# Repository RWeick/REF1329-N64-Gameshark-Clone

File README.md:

# REF1329-N64-Gameshark-Pro-Clone
This is a fully functional Nintendo 64 GameShark clone. It implements the original LZ9FC17 GAL on an Altera EPM240, and fully supports all functionality to include: parallel port, 7 segment display, and the GS button.

The LZ9FC17 GAL is the same for both the N64 Gameshark and the N64 Gameshark Pro. All N64 Gameshark and Action Replay firmwares work with this clone.

This is compatible with the Sanni Cartridge Reader's N64 Gameshark programming function as well as the EMS hacked firmware that was released for the first ever Gameshark / Action Replay clone.

The upper EEPROM contains the high bytes of the BIN, and the lower EEPROM contains the low bytes of the BIN. The 2x5 10 pin connector is mapped to the standard Altera USB Blaster pinout for programming. Happy making.

Huge shoutout to @Parasyte for his ceaseless guidance, mentorship, and encouragement, as well as for originally documenting the hardware registers of the N64 Gameshark. This would not exist without him.

Huge shoutout to the [N64Brew](https://n64brew.dev/wiki/Main_Page) community, who have provided countless resources and documentation that enabled me to complete this project.

Huge shoutout to @Jhynjhiruu for determining that my original reconstruction wasn't perfectly faithful to the original chip. With his discoveries, the logic here is now complete.

The Various Gameshark Firmwares directory contains every known firmware in existence. All US firmwares have been collected and preserved there as well as all of the versions I can find from other countries. Please contribute if you have something I do not! It was no small task to collect the U.S. firmwares as some of those are incredibly rare to find today.

[Here's a video of it in action.](https://youtu.be/faCqaDdL_ds)

[Featured on RetroRGB](https://www.retrorgb.com/libreshark-pro-n64-gameshark.html)

PCB Thickness: 1.2 mm

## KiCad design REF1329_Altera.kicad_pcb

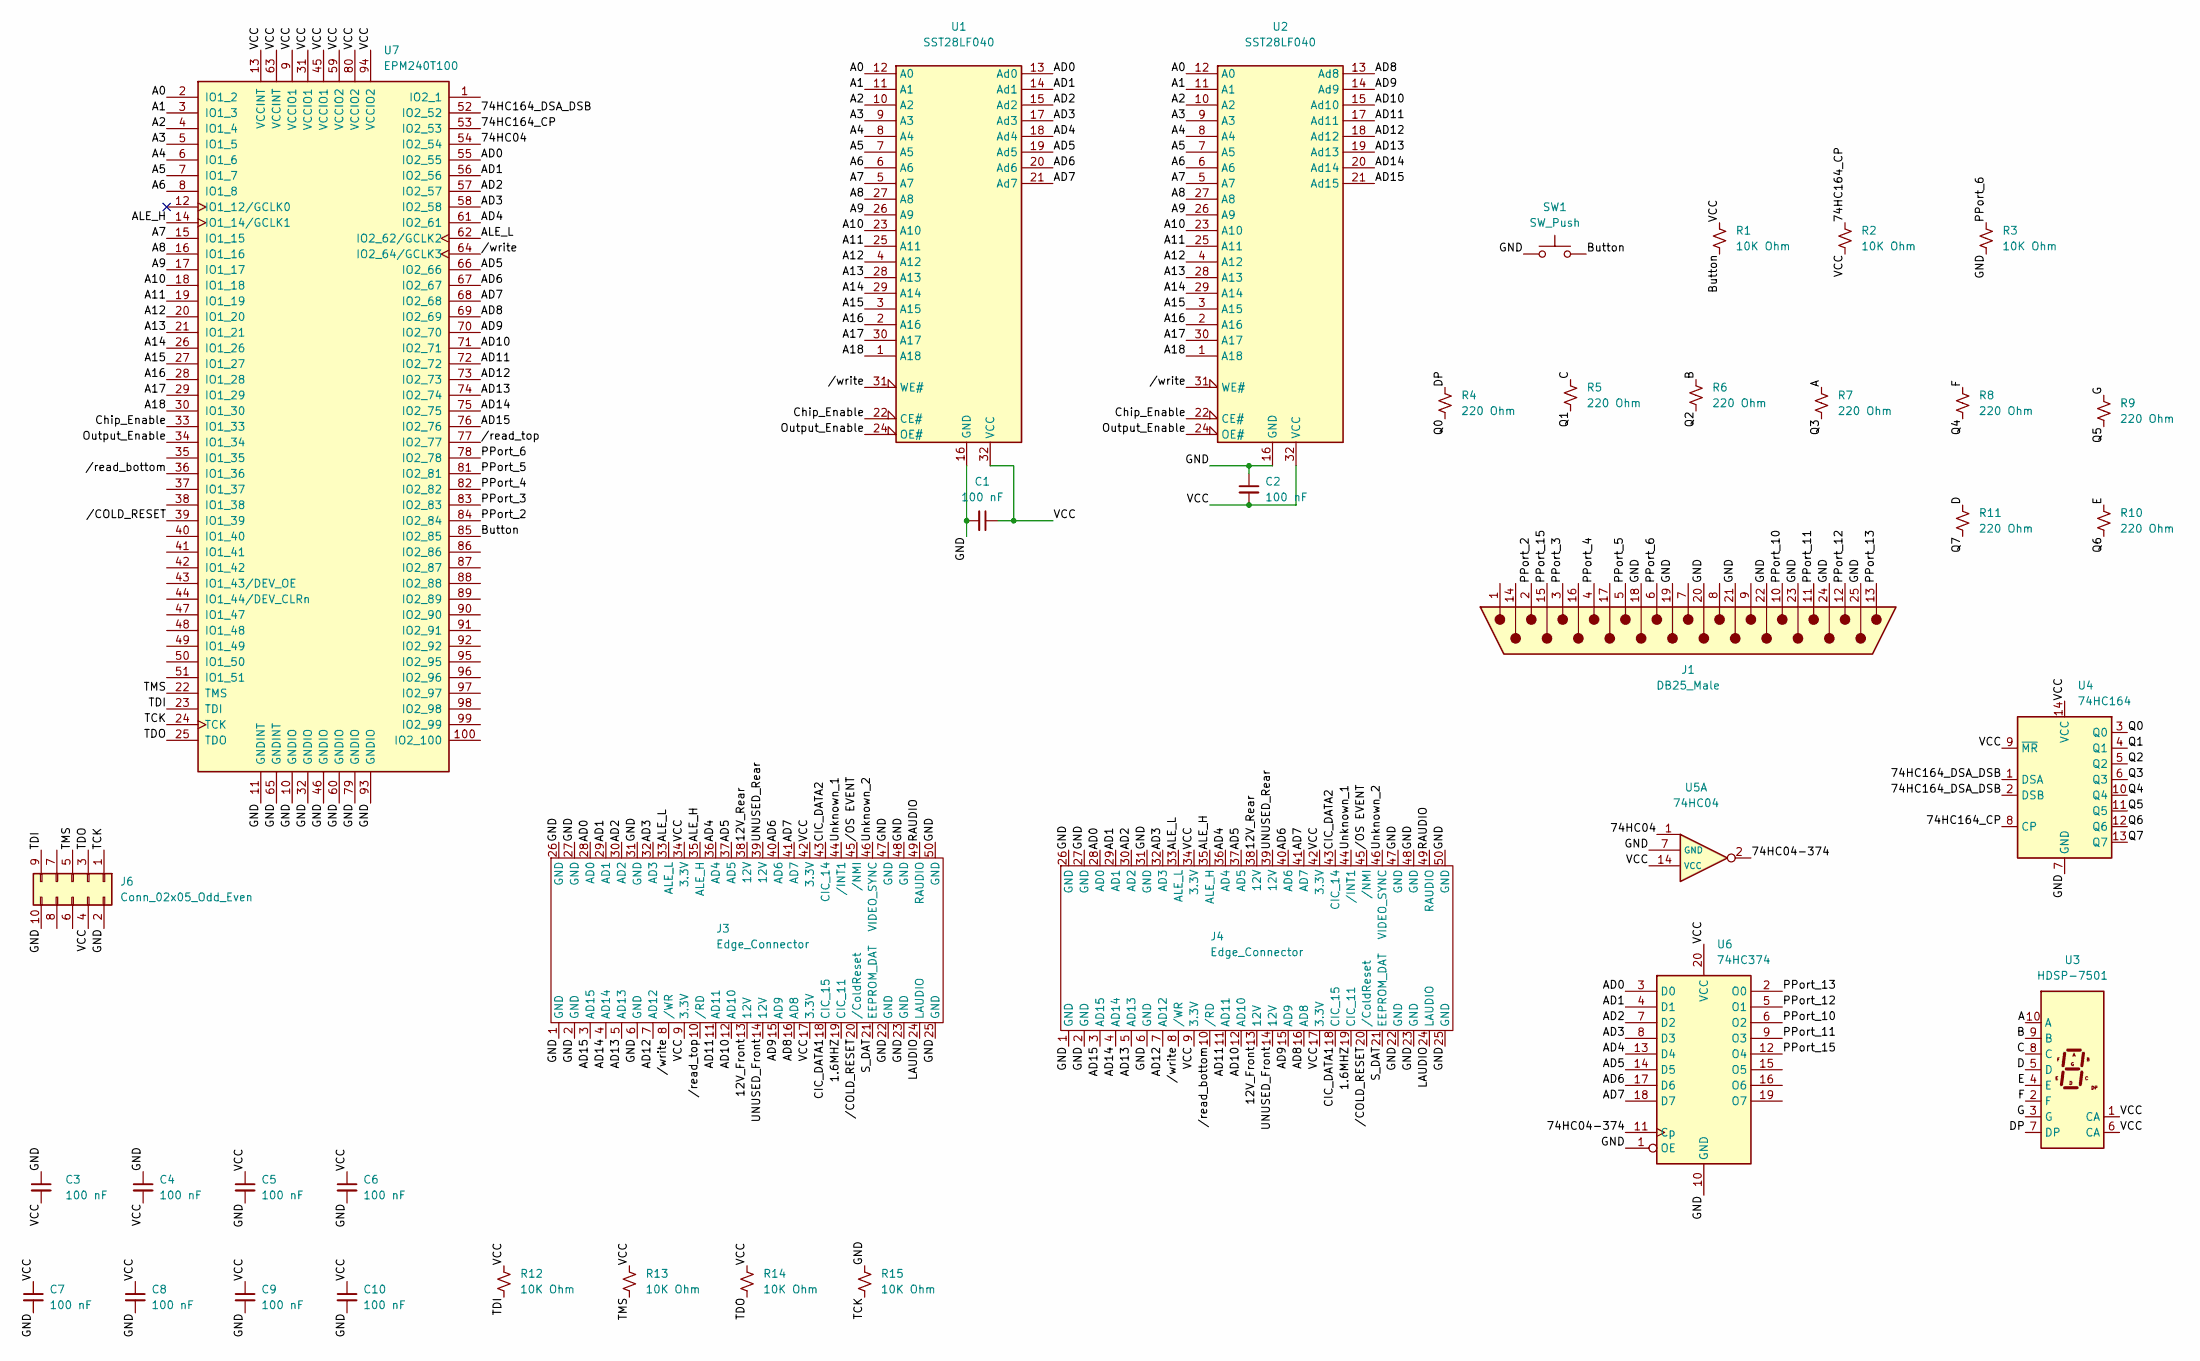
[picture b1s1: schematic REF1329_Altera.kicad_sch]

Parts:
C1, C2: 100 nF; 100 nF Cap
C3, C4, C5, C6, C7, C8, C9, C10: 100 nF; C_0603_1608Metric
J1: DB25_Male; DSUB-25_Male_Vertical_P2.77x2.84mm
J3: Edge_Connector; Top Edge Connector
J4: Edge_Connector; Bottom Edge Connector
J6: Conn_02x05_Odd_Even; IDC-Header_2x05_P2.54mm_Vertical
R1, R2, R3: 10K Ohm; 10k Ohm Resistor
R4, R5, R6, R7, R8, R9, R10, R11: 220 Ohm; 220 Ohm Resistor
R12, R13, R14, R15: 10K Ohm; R_0603_1608Metric
SW1: SW_Push; 1mm Push Button
U1, U2: SST28LF040; PLCC32
U3: HDSP-7501; HDSP-7401
U4: 74HC164
U5: 74HC04; 74HC04M
U6: 74HC374
U7: EPM240T100; EPM240

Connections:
/1.6MHZ: J3.19 (CIC_11), J4.19 (CIC_11)
/12V_Front: J3.13 (12V), J4.13 (12V)
/12V_Rear: J3.38 (12V), J4.38 (12V)
/74HC04: U5.1, U7.54 (IO2_54)
/74HC04-374: U5.2, U6.11 (Cp)
/74HC164_CP: R2.1, U4.8 (CP), U7.53 (IO2_53)
/74HC164_DSA_DSB: U4.1 (DSA), U4.2 (DSB), U7.52 (IO2_52)
/A: R7.1, U3.10 (A)
/A0: U1.12 (A0), U2.12 (A0), U7.2 (IO1_2)
/A1: U1.11 (A1), U2.11 (A1), U7.3 (IO1_3)
/A2: U1.10 (A2), U2.10 (A2), U7.4 (IO1_4)
/A3: U1.9 (A3), U2.9 (A3), U7.5 (IO1_5)
/A4: U1.8 (A4), U2.8 (A4), U7.6 (IO1_6)
/A5: U1.7 (A5), U2.7 (A5), U7.7 (IO1_7)
/A6: U1.6 (A6), U2.6 (A6), U7.8 (IO1_8)
/A7: U1.5 (A7), U2.5 (A7), U7.15 (IO1_15)
/A8: U1.27 (A8), U2.27 (A8), U7.16 (IO1_16)
/A9: U1.26 (A9), U2.26 (A9), U7.17 (IO1_17)
/A10: U1.23 (A10), U2.23 (A10), U7.18 (IO1_18)
/A11: U1.25 (A11), U2.25 (A11), U7.19 (IO1_19)
/A12: U1.4 (A12), U2.4 (A12), U7.20 (IO1_20)
/A13: U1.28 (A13), U2.28 (A13), U7.21 (IO1_21)
/A14: U1.29 (A14), U2.29 (A14), U7.26 (IO1_26)
/A15: U1.3 (A15), U2.3 (A15), U7.27 (IO1_27)
/A16: U1.2 (A16), U2.2 (A16), U7.28 (IO1_28)
/A17: U1.30 (A17), U2.30 (A17), U7.29 (IO1_29)
/A18: U1.1 (A18), U2.1 (A18), U7.30 (IO1_30)
/AD0: J3.28 (AD0), J4.28 (AD0), U1.13 (Ad0), U6.3 (D0), U7.55 (IO2_55)
/AD1: J3.29 (AD1), J4.29 (AD1), U1.14 (Ad1), U6.4 (D1), U7.56 (IO2_56)
/AD2: J3.30 (AD2), J4.30 (AD2), U1.15 (Ad2), U6.7 (D2), U7.57 (IO2_57)
/AD3: J3.32 (AD3), J4.32 (AD3), U1.17 (Ad3), U6.8 (D3), U7.58 (IO2_58)
/AD4: J3.36 (AD4), J4.36 (AD4), U1.18 (Ad4), U6.13 (D4), U7.61 (IO2_61)
/AD5: J3.37 (AD5), J4.37 (AD5), U1.19 (Ad5), U6.14 (D5), U7.66 (IO2_66)
/AD6: J3.40 (AD6), J4.40 (AD6), U1.20 (Ad6), U6.17 (D6), U7.67 (IO2_67)
/AD7: J3.41 (AD7), J4.41 (AD7), U1.21 (Ad7), U6.18 (D7), U7.68 (IO2_68)
/AD8: J3.16 (AD8), J4.16 (AD8), U2.13 (Ad8), U7.69 (IO2_69)
/AD9: J3.15 (AD9), J4.15 (AD9), U2.14 (Ad9), U7.70 (IO2_70)
/AD10: J3.12 (AD10), J4.12 (AD10), U2.15 (Ad10), U7.71 (IO2_71)
/AD11: J3.11 (AD11), J4.11 (AD11), U2.17 (Ad11), U7.72 (IO2_72)
/AD12: J3.7 (AD12), J4.7 (AD12), U2.18 (Ad12), U7.73 (IO2_73)
/AD13: J3.5 (AD13), J4.5 (AD13), U2.19 (Ad13), U7.74 (IO2_74)
/AD14: J3.4 (AD14), J4.4 (AD14), U2.20 (Ad14), U7.75 (IO2_75)
/AD15: J3.3 (AD15), J4.3 (AD15), U2.21 (Ad15), U7.76 (IO2_76)
/ALE_H: J3.35 (ALE_H), J4.35 (ALE_H), U7.14 (IO1_14/GCLK1)
/ALE_L: J3.33 (ALE_L), J4.33 (ALE_L), U7.62 (IO2_62/GCLK2)
/B: R6.1, U3.9 (B)
/Button: R1.1, SW1.2, U7.85 (IO2_85)
/C: R5.1, U3.8 (C)
/CIC_DATA1: J3.18 (CIC_15), J4.18 (CIC_15)
/CIC_DATA2: J3.43 (CIC_14), J4.43 (CIC_14)
/Chip_Enable: U1.22 (CE#), U2.22 (CE#), U7.33 (IO1_33)
/D: R11.1, U3.5 (D)
/DP: R4.1, U3.7 (DP)
/E: R10.1, U3.4 (E)
/F: R8.1, U3.2 (F)
/G: R9.1, U3.3 (G)
/GND: C1.2, C2.1, C3.1, C4.1, C5.2, C6.2, C7.2, C8.2, C9.2, C10.2, J1.18, J1.19, J1.20, J1.21, J1.22, J1.23, J1.24, J1.25, J3.1 (GND), J3.2 (GND), J3.6 (GND), J3.22 (GND), J3.23 (GND), J3.25 (GND), J3.26 (GND), J3.27 (GND), J3.31 (GND), J3.47 (GND), J3.48 (GND), J3.50 (GND), J4.1 (GND), J4.2 (GND), J4.6 (GND), J4.22 (GND), J4.23 (GND), J4.25 (GND), J4.26 (GND), J4.27 (GND), J4.31 (GND), J4.47 (GND), J4.48 (GND), J4.50 (GND), J6.2, J6.10, R3.2, R15.1, SW1.1, U1.16 (GND), U2.16 (GND), U4.7 (GND), U5.7 (GND), U6.1 (OE), U6.10 (GND), U7.10 (GNDIO), U7.11 (GNDINT), U7.32 (GNDIO), U7.46 (GNDIO), U7.60 (GNDIO), U7.65 (GNDINT), U7.79 (GNDIO), U7.93 (GNDIO)
/LAUDIO: J3.24 (LAUDIO), J4.24 (LAUDIO)
/Output_Enable: U1.24 (OE#), U2.24 (OE#), U7.34 (IO1_34)
/PPort_2: J1.2, U7.84 (IO2_84)
/PPort_3: J1.3, U7.83 (IO2_83)
/PPort_4: J1.4, U7.82 (IO2_82)
/PPort_5: J1.5, U7.81 (IO2_81)
/PPort_6: J1.6, R3.1, U7.78 (IO2_78)
/PPort_10: J1.10, U6.6 (O2)
/PPort_11: J1.11, U6.9 (O3)
/PPort_12: J1.12, U6.5 (O1)
/PPort_13: J1.13, U6.2 (O0)
/PPort_15: J1.15, U6.12 (O4)
/Q0: R4.2, U4.3 (Q0)
/Q1: R5.2, U4.4 (Q1)
/Q2: R6.2, U4.5 (Q2)
/Q3: R7.2, U4.6 (Q3)
/Q4: R8.2, U4.10 (Q4)
/Q5: R9.2, U4.11 (Q5)
/Q6: R10.2, U4.12 (Q6)
/Q7: R11.2, U4.13 (Q7)
/RAUDIO: J3.49 (RAUDIO), J4.49 (RAUDIO)
/S_DAT: J3.21 (EEPROM_DAT), J4.21 (EEPROM_DAT)
/TCK: J6.1, R15.2, U7.24 (TCK)
/TDI: J6.9, R12.2, U7.23 (TDI)
/TDO: J6.3, R14.2, U7.25 (TDO)
/TMS: J6.5, R13.2, U7.22 (TMS)
/UNUSED_Front: J3.14 (12V), J4.14 (12V)
/UNUSED_Rear: J3.39 (12V), J4.39 (12V)
/Unknown_1: J3.44 (/INT1), J4.44 (/INT1)
/Unknown_2: J3.46 (VIDEO_SYNC), J4.46 (VIDEO_SYNC)
/VCC: C1.1, C2.2, C3.2, C4.2, C5.1, C6.1, C7.1, C8.1, C9.1, C10.1, J3.9 (3.3V), J3.17 (3.3V), J3.34 (3.3V), J3.42 (3.3V), J4.9 (3.3V), J4.17 (3.3V), J4.34 (3.3V), J4.42 (3.3V), J6.4, R1.2, R2.2, R12.1, R13.1, R14.1, U1.32 (VCC), U2.32 (VCC), U3.1 (CA), U3.6 (CA), U4.9 (~MR), U4.14 (VCC), U5.14 (VCC), U6.20 (VCC), U7.9 (VCCIO1), U7.13 (VCCINT), U7.31 (VCCIO1), U7.45 (VCCIO1), U7.59 (VCCIO2), U7.63 (VCCINT), U7.80 (VCCIO2), U7.94 (VCCIO2)
//COLD_RESET: J3.20 (/ColdReset), J4.20 (/ColdReset), U7.39 (IO1_39)
//OS EVENT: J3.45 (/NMI), J4.45 (/NMI)
//read_bottom: J4.10 (/RD), U7.36 (IO1_36)
//read_top: J3.10 (/RD), U7.77 (IO2_77)
//write: J3.8 (/WR), J4.8 (/WR), U1.31 (WE#), U2.31 (WE#), U7.64 (IO2_64/GCLK3)

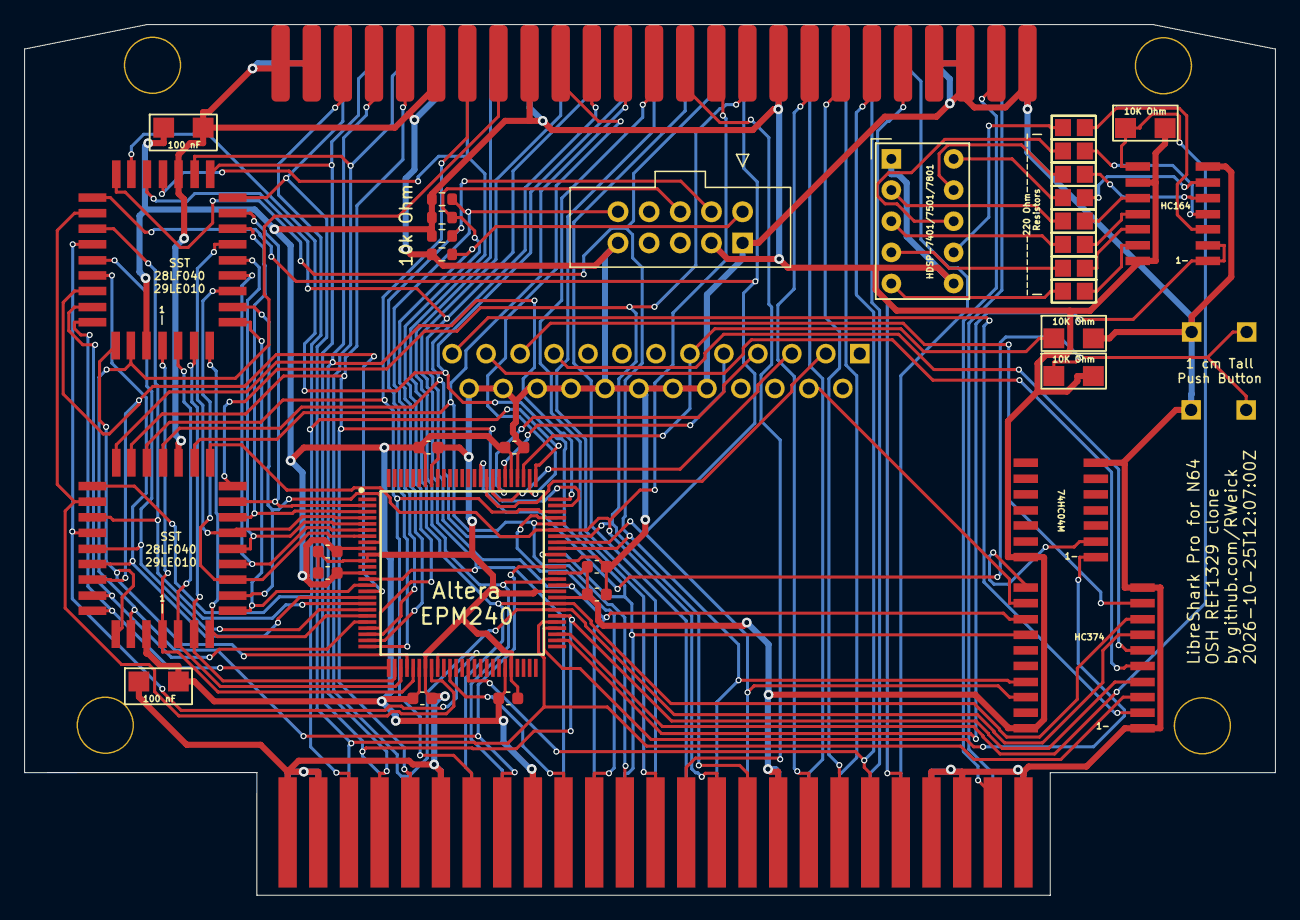
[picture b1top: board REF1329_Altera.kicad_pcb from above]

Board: 2 copper layers, 102.0 x 71.0 mm, 41 parts (1 on the bottom side), 93 nets.

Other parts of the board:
Hole1, Hole2, Hole3, Hole4: N64-Hole

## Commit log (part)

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2023-01-13 Add files via upload
    Verilog that allows this Gameshark implementation to be programmed and read by a Sanni Cart Reader. You will need to reprogram it again afterwards with the Verilog for use with the N64.
2023-05-17 Add .gitignore for local KiCad files
2023-05-17 Add RWeick, LibreShark, and timestamp to PCB silkscreen
    Also make existing silkscreen text larger and avoid overlapping with holes in the board
2023-05-17 Relative path to PCB image in README
2023-05-17 Add image alt text
2023-07-05 Update README.md
    Add a demo video
2024-02-19 Rename N64 Gameshark v3.3.bin to N64 Gameshark Pro v3.3.bin
2024-05-10 Update README.md
    Completely rewrote verilog. Improved stability and created compatibility with the Sanni Cart Reader and N64 simultaneously.
2024-07-06 Update README.md
    Fixed, thanks Gent!
2024-07-13 Add files via upload
    Fixed naming convention
